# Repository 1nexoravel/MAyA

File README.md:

# MAyA
IoT - coleira e alimentador para animais.
Projeto antigo e incompleto feito no meio da minha gradução para o mestrado de Engenharia de Software de outra pessoa. 
Arduino Uno, Raspberry Pi, ESP32.
Linguagens usadas: C, Python.

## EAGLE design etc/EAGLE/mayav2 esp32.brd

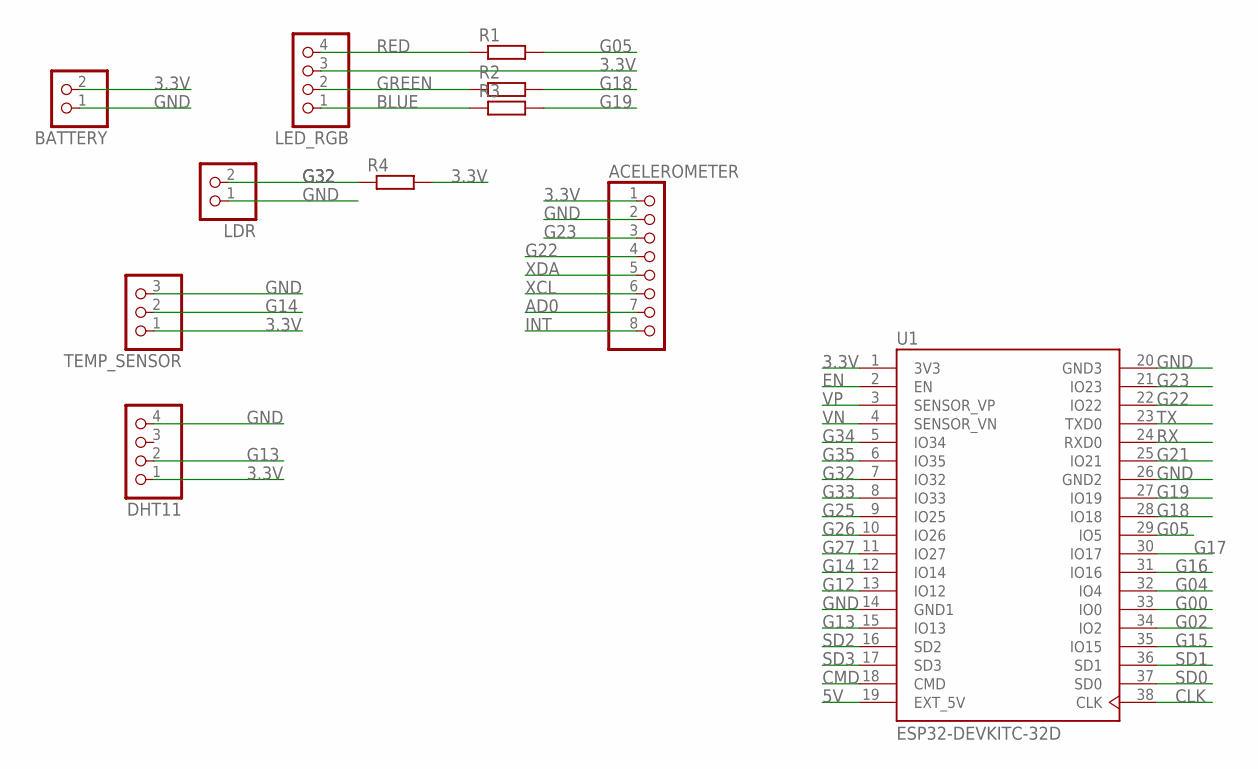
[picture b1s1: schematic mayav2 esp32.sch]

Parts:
ACELEROMETER: PINHD-1X8; 1X08
BATTERY: PINHD-1X2; 1X02
DHT11: PINHD-1X4; 1X04
LDR: PINHD-1X2; 1X02
LED_RGB: PINHD-1X4; 1X04
R1, R2, R3, R4: R-EU_0204/7; 0204/7
TEMP_SENSOR: PINHD-1X3; 1X03
U1: ESP32-DEVKITC-32D; MODULE_ESP32-DEVKITC-32D

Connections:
3.3V: ACELEROMETER.1, BATTERY.2, DHT11.1, LED_RGB.3, R4.2, TEMP_SENSOR.1, U1.1 (3V3)
5V: U1.19 (EXT_5V)
AD0: ACELEROMETER.7
BLUE: LED_RGB.1, R3.1
CLK: U1.38 (CLK)
CMD: U1.18 (CMD)
EN: U1.2 (EN)
G00: U1.33 (IO0)
G02: U1.34 (IO2)
G04: U1.32 (IO4)
G05: R1.2, U1.29 (IO5)
G12: U1.13 (IO12)
G13: DHT11.2, U1.15 (IO13)
G14: TEMP_SENSOR.2, U1.12 (IO14)
G15: U1.35 (IO15)
G16: U1.31 (IO16)
G17: U1.30 (IO17)
G18: R2.2, U1.28 (IO18)
G19: R3.2, U1.27 (IO19)
G21: U1.25 (IO21)
G22: ACELEROMETER.4, U1.22 (IO22)
G23: ACELEROMETER.3, U1.21 (IO23)
G25: U1.9 (IO25)
G26: U1.10 (IO26)
G27: U1.11 (IO27)
G32: LDR.2, R4.1, U1.7 (IO32)
G33: U1.8 (IO33)
G34: U1.5 (IO34)
G35: U1.6 (IO35)
GND: ACELEROMETER.2, BATTERY.1, DHT11.4, LDR.1, TEMP_SENSOR.3, U1.14 (GND1), U1.20 (GND3), U1.26 (GND2)
GREEN: LED_RGB.2, R2.1
INT: ACELEROMETER.8
RED: LED_RGB.4, R1.1
RX: U1.24 (RXD0)
SD0: U1.37 (SD0)
SD1: U1.36 (SD1)
SD2: U1.16 (SD2)
SD3: U1.17 (SD3)
TX: U1.23 (TXD0)
VN: U1.4 (SENSOR_VN)
VP: U1.3 (SENSOR_VP)
XCL: ACELEROMETER.6
XDA: ACELEROMETER.5

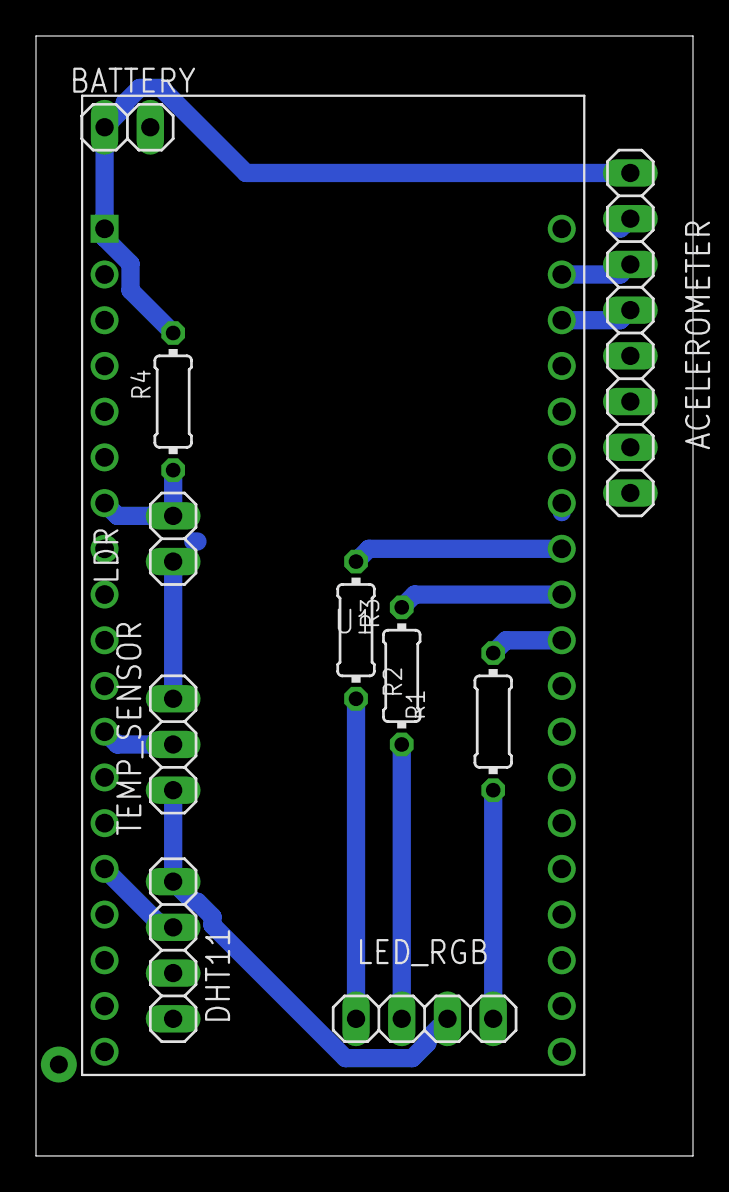
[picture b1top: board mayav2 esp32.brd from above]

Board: 2 copper layers, 36.5 x 62.2 mm, 11 parts (0 on the bottom side), 13 nets.

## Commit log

2020-01-27 Tudo
    01/08/2019
2020-01-27 0.2
    Tudo
